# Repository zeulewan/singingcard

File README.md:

# KiCad Agent Experiment

An experiment to have Claude Code autonomously design and order PCBs from start to finish.

## Goal

Given project requirements (e.g., "make an ESP32 dev board with USB-C and 3 GPIO LEDs"), Claude Code should be able to:

1. Research and select appropriate components from JLCPCB's library
2. Design the schematic with proper connections
3. Create the PCB layout
4. Auto-route the traces
5. Run DRC/ERC checks
6. Generate fabrication files
7. Order the PCB via JLCPCB API

The human should only need to:
- Provide initial requirements
- Set up API keys
- Occasionally review/approve major decisions

## Status

**Setup Phase** - Installing tools and creating workflow documentation.

## Structure

```
singingcard/
├── kicad/              # KiCad project files
├── docs/               # Documentation and notes
├── venv/               # Python virtual environment
└── .claude/skills/     # Claude skill for KiCad workflow
```

## Tools

See `docs/tool-setup.md` for installed tools and configuration.

---

## Board Design

<div align="center">
  <div>

    <p><em>3D Render</em></p>
  </div>
  <br>

  <div>
    <br>
    <p><em>Schematic</em></p>
  </div>
  <br>

  <div>
    
    <br>
    <em>PCB Layout</em>
  </div>
</div>

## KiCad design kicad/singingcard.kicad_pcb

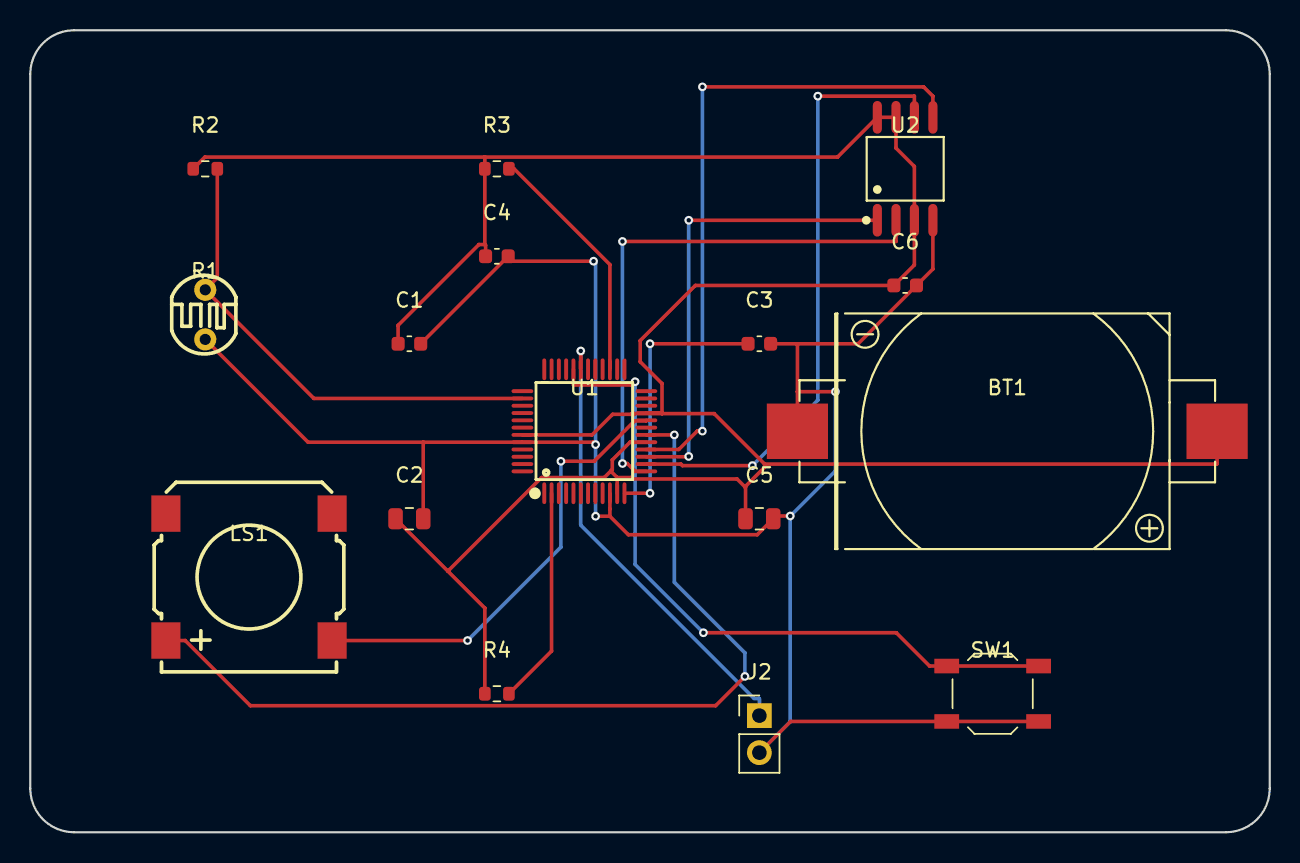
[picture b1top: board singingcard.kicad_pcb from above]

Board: 2 copper layers, 85.0 x 55.0 mm, 16 parts (0 on the bottom side), 14 nets.

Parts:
BT1: CR2032; BAT-TH_CR2032-BS-6-1
C1, C4, C6: 100nF; C_0603_1608Metric
C2, C5: 10uF; C_0805_2012Metric
C3: 1uF; C_0603_1608Metric
J2: Pull-Tab; PinHeader_1x02_P2.54mm_Vertical
LS1: KLJ-01304T-08R07W; BUZ-SMD_4P-L13.0-W13.0-P11.4-BL
R1: GL5528; RES-TH_L5.1-W4.3-P3.40-D0.5
R2, R3, R4: 10k; R_0603_1608Metric
SW1: Button; SW_SPST_TL3342
U1: ISD3900FYI; LQFP-48_L7.0-W7.0-P0.50-LS9.0-BL
U2: W25Q16JVSSIQ; SOIC-8_L5.3-W5.3-P1.27-LS8.0-BL

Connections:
+3V: BT1.1, C1.1, C2.1, C4.1, C5.1, C6.1, R2.1, R3.1, R4.1, U1.11, U1.17, U1.21, U1.43, U2.3, U2.7, U2.8
CSB: R4.2, U1.2
GND: BT1.2, C1.2, C2.2, C3.2, C4.2, C5.2, C6.2, J2.2, R1.2, SW1.2, U1.10, U1.44, U2.4
GPIO0_LDR: R1.1, R2.2, U1.38
GPIO1_BTN: SW1.1, U1.32
GPIO2_TAB: J2.1, U1.31
unnamed: LS1.1, U1.18
unnamed: LS1.2, U1.20
RESET: R3.2, U1.27
SPI_CS: U1.15, U2.1
SPI_MISO: U1.13, U2.2
SPI_MOSI: U1.16, U2.5
SPI_SCK: U1.14, U2.6
VREG: C3.1, U1.12

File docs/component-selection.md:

# Component Selection: Singing Birthday Card Module

## Approach Selected

**SPI Programming Station** - Each card's flash chip is programmed with custom audio before use.

- Audio chip: ISD3900FYI (playback only, built-in speaker amp)
- Storage: Winbond W25Q SPI flash
- Trigger: GL5528 LDR + optional button + pull-tab
- Power: CR2032 (3V)

## Research Findings

### Audio Chips - LCSC Availability

#### NOT Available on LCSC:
| Chip | Notes |
|------|-------|
| MH2024K-24SS | MP3 + USB mass storage - **NOT ON LCSC** |
| WT2003S | MP3 + USB mass storage - **NOT ON LCSC** |
| JQ6500 | Popular MP3 module - **NOT ON LCSC** |
| ISD1820 | Classic voice record chip - **NOT ON LCSC** |
| WT588D | Voice chip - **DISCONTINUED** |

#### Available on LCSC (Voice Record/Playback):
| Part Number | LCSC# | Price | Stock | Features | Voltage |
|-------------|-------|-------|-------|----------|---------|
| ISD3900FYI | C2613393 | $1.29 | 60 | I2S/SPI, 4-48kHz, playback only, ext flash | 2.7-3.6V |
| ISD3800FYI | C2613397 | $2.07 | 2 | I2S/SPI, 4-48kHz, playback only | 2.7-5.5V |
| ISD1730SY | C2613883 | $4.84 | 10 | SPI, 4-12kHz, record/playback | 2.4-5.5V |

**Note**: ISD chips are designed for voice prompts (low bitrate), not MP3 music playback. They require external flash for longer recordings and don't have USB mass storage.

### Light Sensor (LDR) - Available on LCSC
| Part Number | LCSC# | Price (10+) | Stock | Specs |
|-------------|-------|-------------|-------|-------|
| GL5528 | C125627 | $0.049 | 23,570 | 540nm, 10-20kΩ, Through-hole 3mm |
| GL5528 | C10081 | $0.039 | 10,250 | 540nm, 8-20kΩ, Through-hole 3.4mm |

**Selected**: C10081 (JCHL) - $0.039, good stock

### CR2032 Battery Holder - Available on JLCPCB Parts
| Part Number | JLCPCB# | Price (1+) | Stock | Type |
|-------------|---------|------------|-------|------|
| CR2032-BS-6-1 | C70377 | $0.17 | 48,239 | SMD |

**Selected**: C70377 - Good stock, SMD mount

### Speakers - To Be Selected
Need: 23-28mm, 8Ω, 0.5-1W
LCSC has 1,400+ speaker options but requires manual filtering.

---

## Three Possible Approaches

### Option A: Simple Voice Chip (Cheapest, No USB)
Use ISD-series or similar voice playback chip.

**Pros:**
- Works with 3V CR2032
- Available on LCSC
- ~$1-2 per chip

**Cons:**
- No USB drag-and-drop upload
- Audio must be pre-programmed via SPI programmer
- Lower audio quality (voice-optimized, not music)

**Good for:** Pre-recorded message cards where audio doesn't change

### Option B: MP3 Module from AliExpress (USB, but Not LCSC)
Source MH2024K or WT2003S module from AliExpress/Alibaba.

**Pros:**
- USB drag-and-drop MP3 upload
- Good audio quality
- Trigger pins available

**Cons:**
- Not available on LCSC (can't do JLCPCB SMT assembly)
- Requires 4.5-5V (NOT compatible with single CR2032)
- Need boost converter or 2x CR2032 in series
- Module cost: ~$1-2 from China

**Good for:** DIY projects where you source modules separately

### Option C: Hybrid PCB + Module
Design PCB with LDR, triggers, battery holder, and space to solder an MP3 module.

**Pros:**
- Can use JLCPCB for PCB fab
- Flexibility to source audio module separately
- Works with existing $1-2 MP3 modules from China

**Cons:**
- Two-stage assembly (PCB + module)
- Still needs 2x CR2032 or LiPo for 5V module
- Total cost likely >$3/unit

---

## Recommendation

Given the requirements, I recommend **reconsidering one of these constraints**:

1. **Drop USB requirement** → Use ISD chip with pre-programmed audio
2. **Change battery to 2x CR2032 or small LiPo** → Can use USB-capable MP3 chip
3. **Accept non-LCSC sourcing** → Buy MH2024K modules from AliExpress

## Next Steps

User decision needed:
- [ ] Which approach to pursue?
- [ ] Is pre-programmed audio acceptable? (no USB)
- [ ] Can we use 2x batteries or different power source?
- [ ] Is non-LCSC module sourcing acceptable?

---

## Final Parts List (BOM)

| Component | Part Number | LCSC/JLCPCB | Qty | Unit Price | Notes |
|-----------|-------------|-------------|-----|------------|-------|
| Audio IC | ISD3900FYI | C2613393 | 1 | $1.29 | 48-LQFP, 2.7-3.6V, built-in Class D amp |
| SPI Flash | W25Q16JVSSIQ | TBD | 1 | $0.57 | 16Mbit, 2.7-3.6V, SOIC-8 |
| LDR | GL5528 | C10081 | 1 | $0.04 | Light sensor, through-hole |
| Battery Holder | CR2032-BS-6-1 | C70377 | 1 | $0.17 | SMD |
| Speaker | 23mm 8Ω 0.5W | LCSC (TBD) | 1 | $0.45-0.82 | Electromagnetic |
| Crystal | 11.2896MHz | TBD | 1 | ~$0.15 | For audio timing |
| Tactile Switch | 6x6mm | TBD | 1 | ~$0.02 | Optional button trigger |
| Capacitors | 0.1uF, 10uF, etc | TBD | ~5 | ~$0.05 | Decoupling, audio |
| Resistors | Various | TBD | ~4 | ~$0.02 | LDR divider, etc |
| **Subtotal** | | | | **~$2.85** | Components only |

### PCB Cost Estimate
- PCB fab: ~$0.50-1.00/unit at qty 10 (JLCPCB)
- SMT assembly: ~$0.50/unit (extended parts fee)

**Estimated Total: ~$3.50-4.00/unit** (slightly over $3 target)

---

## ISD3900FYI Key Features

From datasheet:
- **Voltage**: 2.7-3.6V (works with 3V CR2032)
- **Speaker output**: Built-in Class D, 350mW @ 3.3V into 8Ω
- **Audio format**: ADPCM (4-bit) or PCM (12-bit)
- **Sample rates**: 8-48kHz
- **Storage**: Up to 128Mbit external SPI flash (64 min @ 8kHz ADPCM)
- **Standby**: ~1µA
- **Package**: LQFP-48 (7x7mm)

### Flash Storage Calculation
W25Q16 = 16Mbit = 2MB storage

| Sample Rate | Compression | Duration |
|------------|-------------|----------|
| 8kHz | 4-bit ADPCM | ~8 min |
| 16kHz | 4-bit ADPCM | ~4 min |
| 32kHz | 8-bit PCM | ~1 min |
| 48kHz | 8-bit PCM | ~40 sec |

For 10-20 second audio at decent quality (16-32kHz), W25Q16 is plenty.

---

## SPI Programming Setup

To program custom audio for each card:

1. **Hardware needed**:
   - CH341A USB programmer (~$5) OR
   - Raspberry Pi with SPI interface

2. **Software**:
   - Nuvoton ISD-DMK tools for audio conversion
   - flashrom or similar for SPI flash programming

3. **Process**:
   - Convert MP3/WAV to ISD ADPCM format
   - Program flash chip via SPI
   - Assemble card with programmed flash

---

## Next Steps

- [ ] Confirm exact LCSC part numbers for all components
- [ ] Create KiCad schematic
- [ ] Design PCB layout (~85x55mm)
- [ ] Generate Gerbers and BOM
- [ ] Order prototype batch from JLCPCB

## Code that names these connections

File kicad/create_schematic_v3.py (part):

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    'GND': [('BT1', '2'), ('U1', '16'), ('U2', '4'),
            ('C1', '2'), ('C2', '2'), ('C3', '2'), ('C4', '2'), ('C5', '2'), ('C6', '2'),
            ('SW1', '2')],
    'GPIO0_LDR': [('U1', '21'), ('R1', '1'), ('R2', '2')],
    'GPIO1_BTN': [('U1', '27'), ('SW1', '1')],
    'GPIO2_TAB': [('U1', '31'), ('R3', '2')],
    'RESET': [('U1', '12'), ('R4', '2')],
    'SPI_CS': [('U1', '38'), ('U2', '1')],
    'SPI_MOSI': [('U1', '43'), ('U2', '5')],
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
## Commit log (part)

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2025-12-31 Initial setup: KiCad agent workflow for autonomous PCB design
    - Research document with comprehensive tool analysis
    - Claude skill for PCB design workflow
    - Tool setup documentation
    - Workflow quick reference
    - Python venv with kicad-python, skidl, kibot, easyeda2kicad
2025-12-31 Update KiCad images
